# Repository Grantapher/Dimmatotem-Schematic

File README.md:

# Dimmatotem-Schematic
PCB Schematic in EAGLE for one of my arduino projects https://github.com/Grantapher/arduino-all

# Schematic

## Materials
* [Arduino Nanos (2 needed)](https://smile.amazon.com/gp/product/B07DYJPTK7/)
* [WS2812B LED Strip](https://smile.amazon.com/gp/product/B01LSF4Q0A/)
* [Microphone](https://smile.amazon.com/gp/product/B00SLYAI9K/)
* [Rotary Encoders](https://www.sparkfun.com/products/9117)
* [Capacitors](https://smile.amazon.com/gp/product/B06XRDWF5X/)
* [Resistors](https://smile.amazon.com/gp/product/B072BL2VX1/)
* [Breadboards](https://smile.amazon.com/gp/product/B01EV6LJ7G/)
* [Various Jumper Wires](https://smile.amazon.com/gp/product/B01EV70C78/)

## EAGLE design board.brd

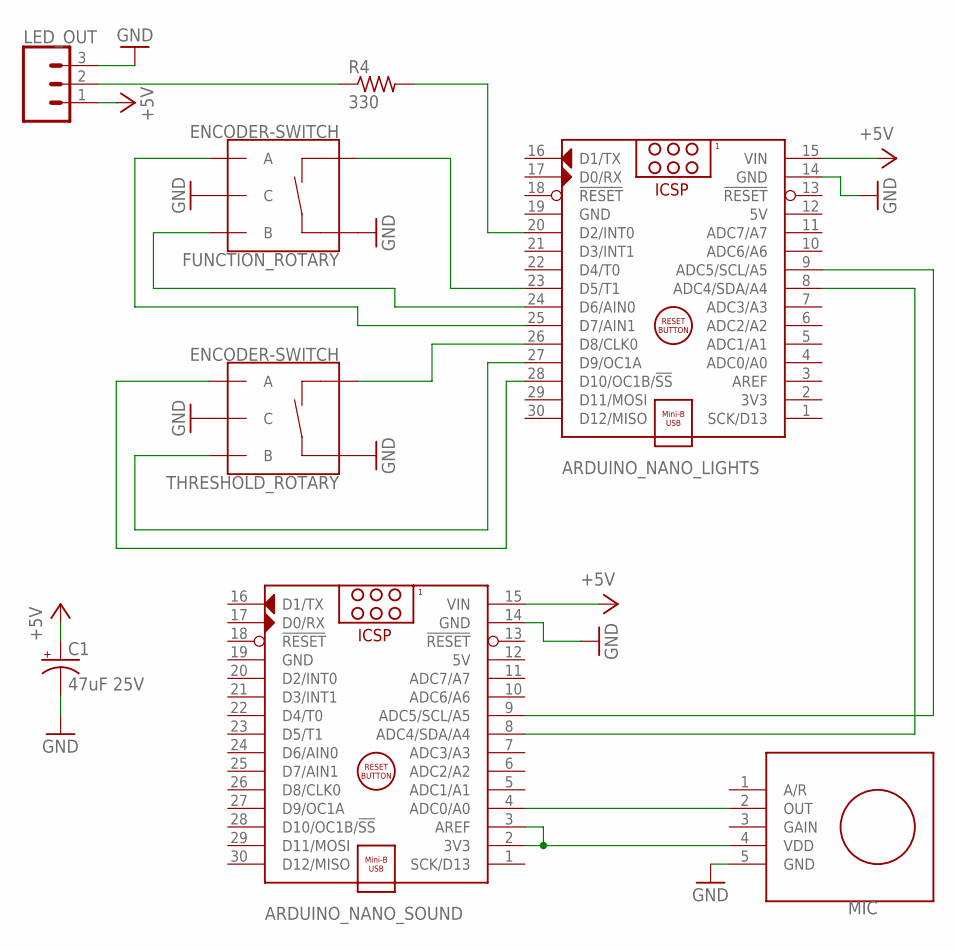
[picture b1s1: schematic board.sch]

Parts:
ARDUINO_NANO_LIGHTS: ARDUINO_NANO
ARDUINO_NANO_SOUND: ARDUINO_NANO
C1: 47uF 25V; E2-5
FUNCTION_ROTARY: ENCODER-SWITCH; ROTARY_ENC_PLAIN
LED_OUT: CONN_03; 1X03
MIC: ADAFRUIT_ELECTRET_MIC_MAX9817
R4: 330; 0207/7
THRESHOLD_ROTARY: ENCODER-SWITCH; ROTARY_ENC_PLAIN

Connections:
5V: ARDUINO_NANO_LIGHTS.12 (5V), ARDUINO_NANO_SOUND.12 (5V)
+5V: ARDUINO_NANO_LIGHTS.15 (VIN), ARDUINO_NANO_SOUND.15 (VIN), C1.+, LED_OUT.1
GND: ARDUINO_NANO_LIGHTS.14 (GND), ARDUINO_NANO_LIGHTS.19 (GND), ARDUINO_NANO_SOUND.14 (GND), ARDUINO_NANO_SOUND.19 (GND), C1.-, FUNCTION_ROTARY.C, FUNCTION_ROTARY.SW+, LED_OUT.3, MIC.5 (GND), THRESHOLD_ROTARY.C, THRESHOLD_ROTARY.SW+
LED_OUT: ARDUINO_NANO_LIGHTS.20 (D2/INT0), R4.2
MIC_VCC: ARDUINO_NANO_SOUND.2 (3V3), ARDUINO_NANO_SOUND.3 (AREF), MIC.4 (VDD)
unnamed: ARDUINO_NANO_LIGHTS.26 (D8/CLK0), THRESHOLD_ROTARY.SW-
unnamed: ARDUINO_NANO_LIGHTS.27 (D9/OC1A), THRESHOLD_ROTARY.B
unnamed: ARDUINO_NANO_LIGHTS.23 (D5/T1), FUNCTION_ROTARY.SW-
unnamed: ARDUINO_NANO_LIGHTS.24 (D6/AIN0), FUNCTION_ROTARY.B
unnamed: ARDUINO_NANO_SOUND.4 (ADC0/A0), MIC.2 (OUT)
unnamed: ARDUINO_NANO_LIGHTS.9 (ADC5/SCL/A5), ARDUINO_NANO_SOUND.9 (ADC5/SCL/A5)
unnamed: ARDUINO_NANO_LIGHTS.25 (D7/AIN1), FUNCTION_ROTARY.A
unnamed: ARDUINO_NANO_LIGHTS.28 (D10/OC1B/!SS), THRESHOLD_ROTARY.A
unnamed: ARDUINO_NANO_LIGHTS.8 (ADC4/SDA/A4), ARDUINO_NANO_SOUND.8 (ADC4/SDA/A4)
unnamed: LED_OUT.2, R4.1

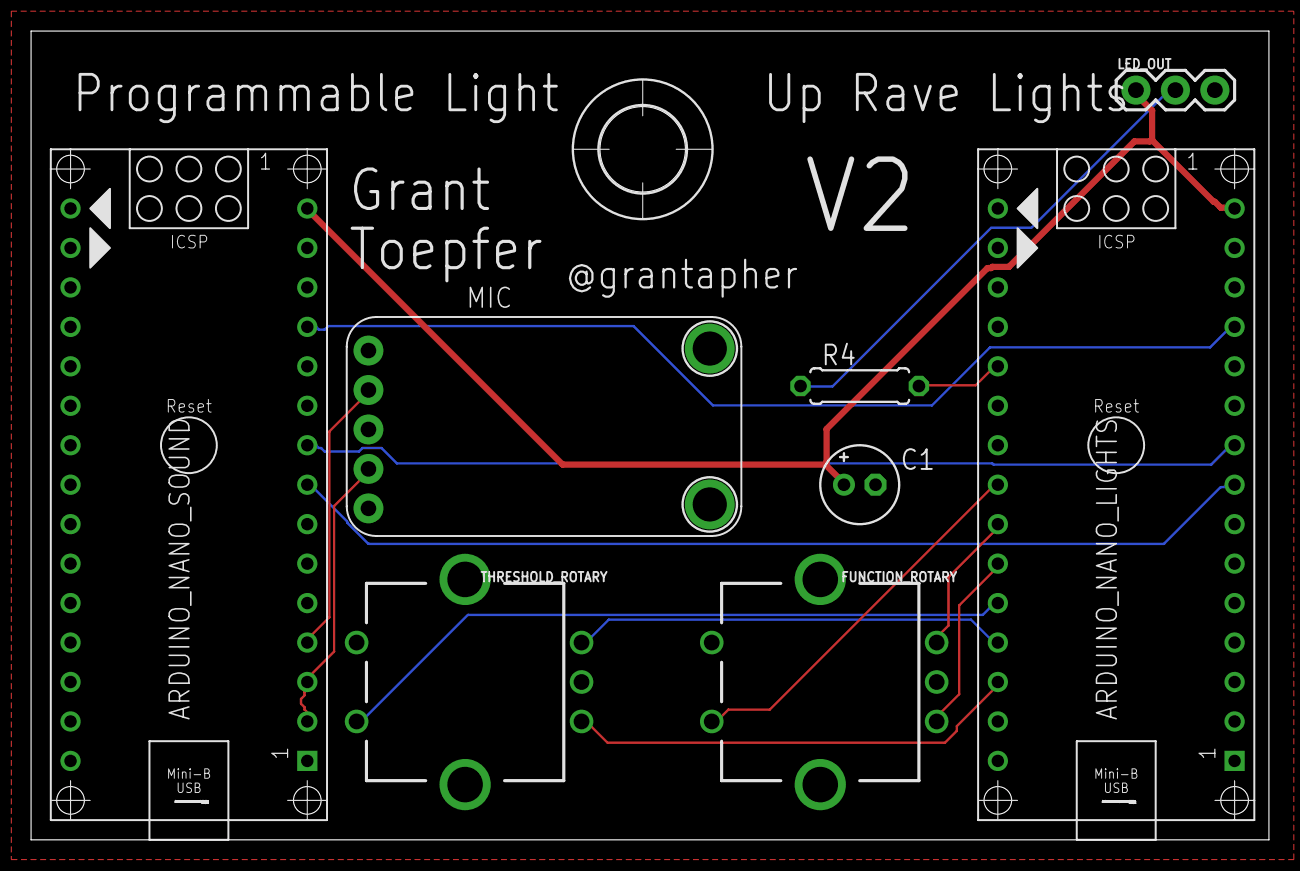
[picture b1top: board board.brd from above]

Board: 2 copper layers, 79.7 x 52.1 mm, 9 parts (0 on the bottom side), 15 nets.

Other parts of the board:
U$1: 5,5

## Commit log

2019-05-08 Adding Board and Schematic
2019-05-14 fixing mistakes from prototype
2019-05-16 Adding library for mic
2019-05-16 Updating schematic
2019-06-04 V2, applying learnings from V1

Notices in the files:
parts and their libraries:
SparkFun-Switches: Licensing: Creative Commons ShareAlike 4.0 International - https://creativecommons.org/licenses/by-sa/4.0
